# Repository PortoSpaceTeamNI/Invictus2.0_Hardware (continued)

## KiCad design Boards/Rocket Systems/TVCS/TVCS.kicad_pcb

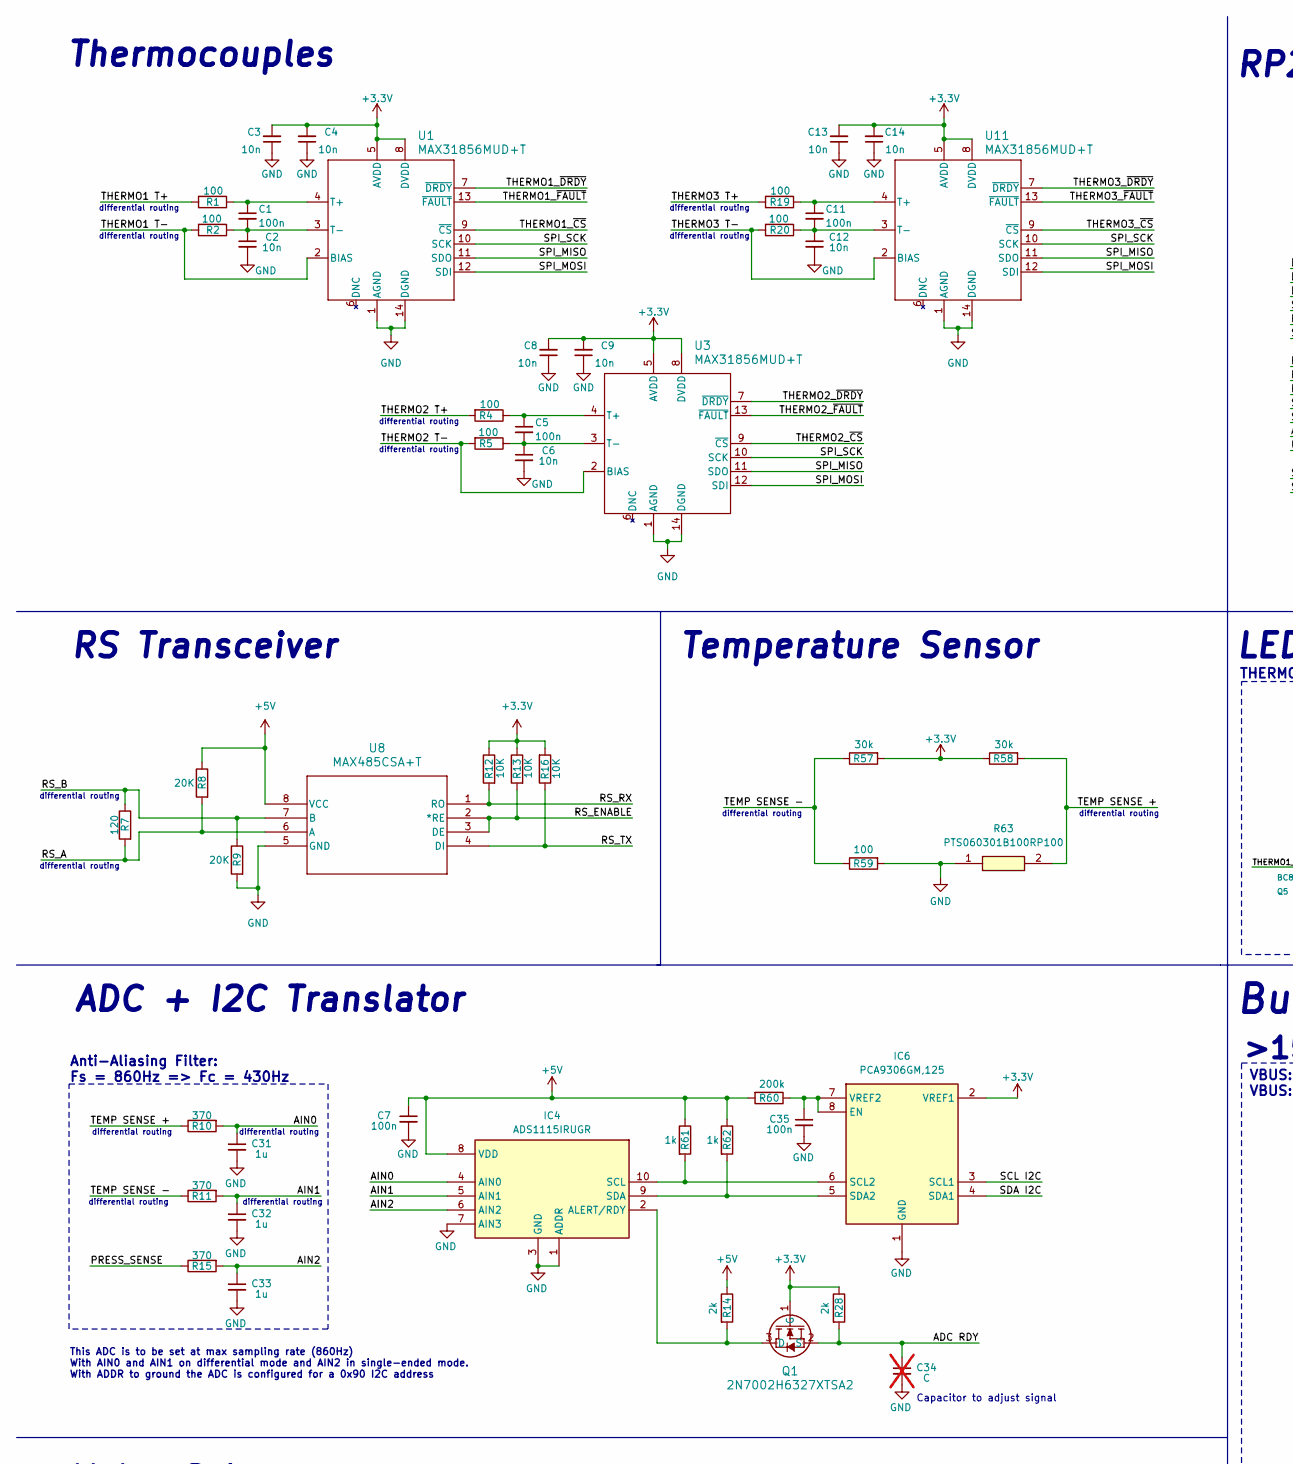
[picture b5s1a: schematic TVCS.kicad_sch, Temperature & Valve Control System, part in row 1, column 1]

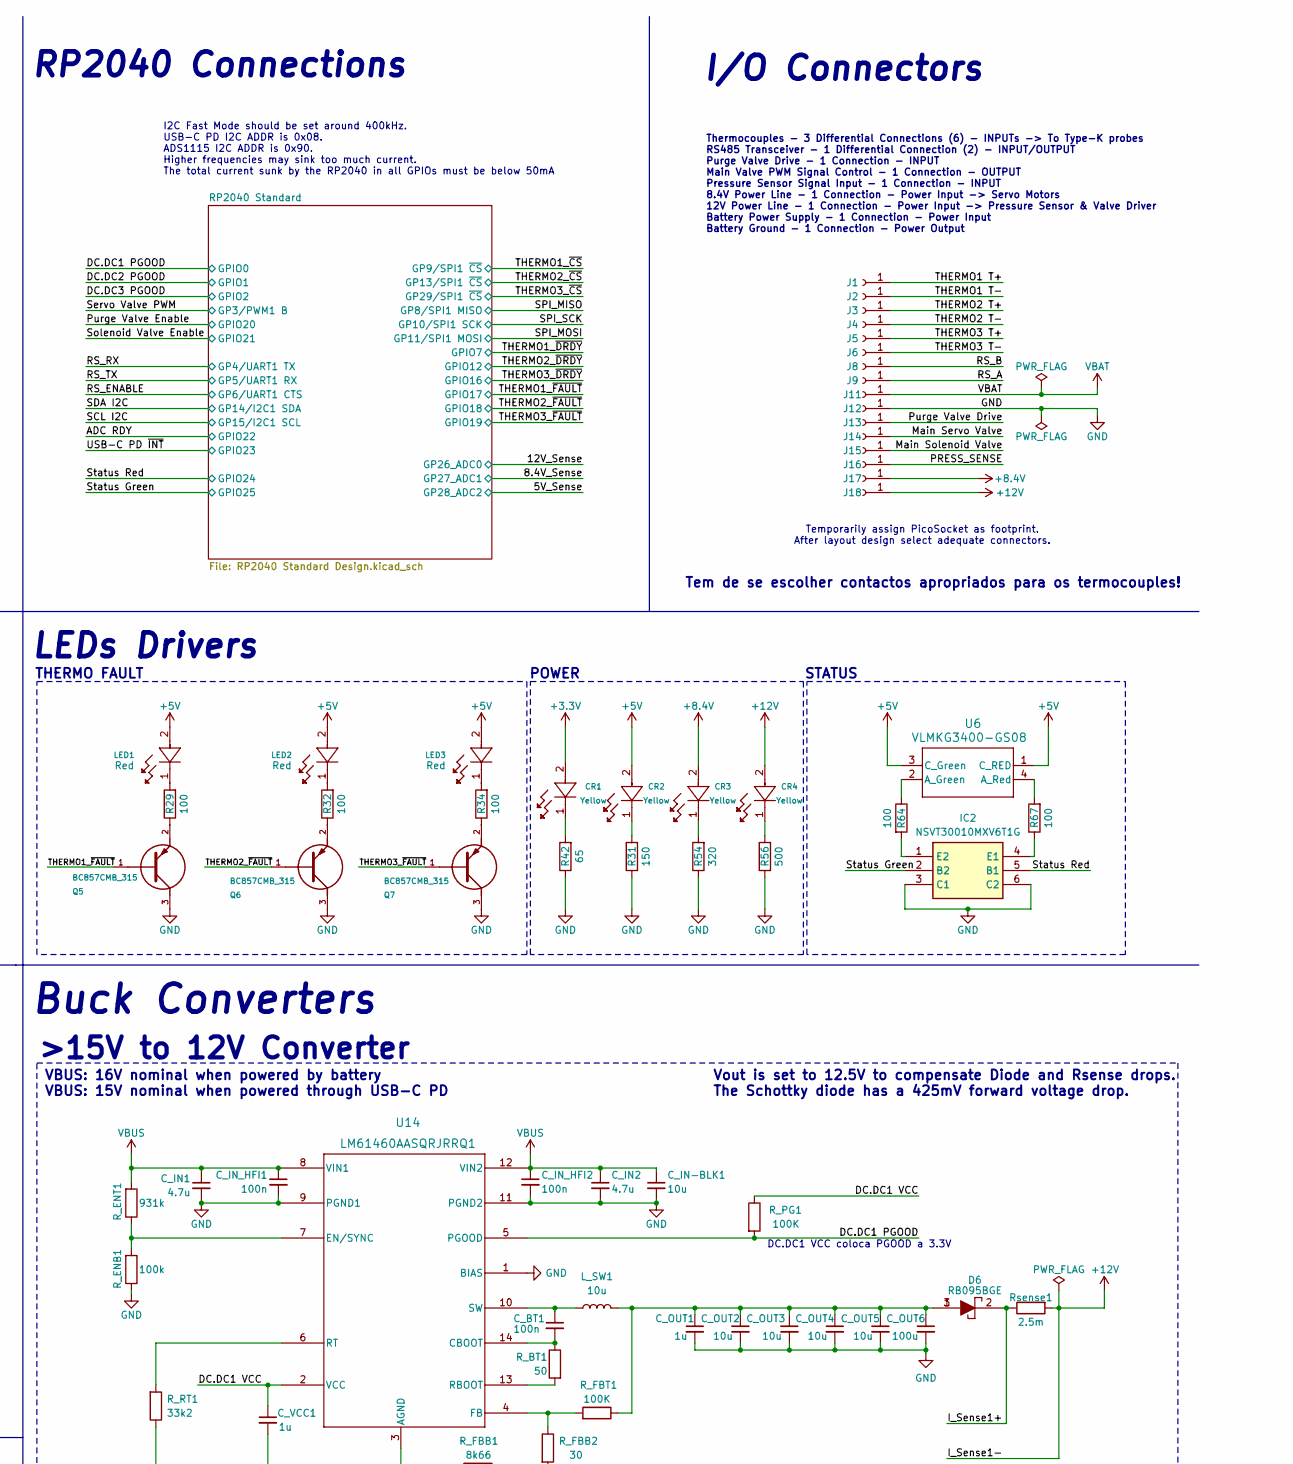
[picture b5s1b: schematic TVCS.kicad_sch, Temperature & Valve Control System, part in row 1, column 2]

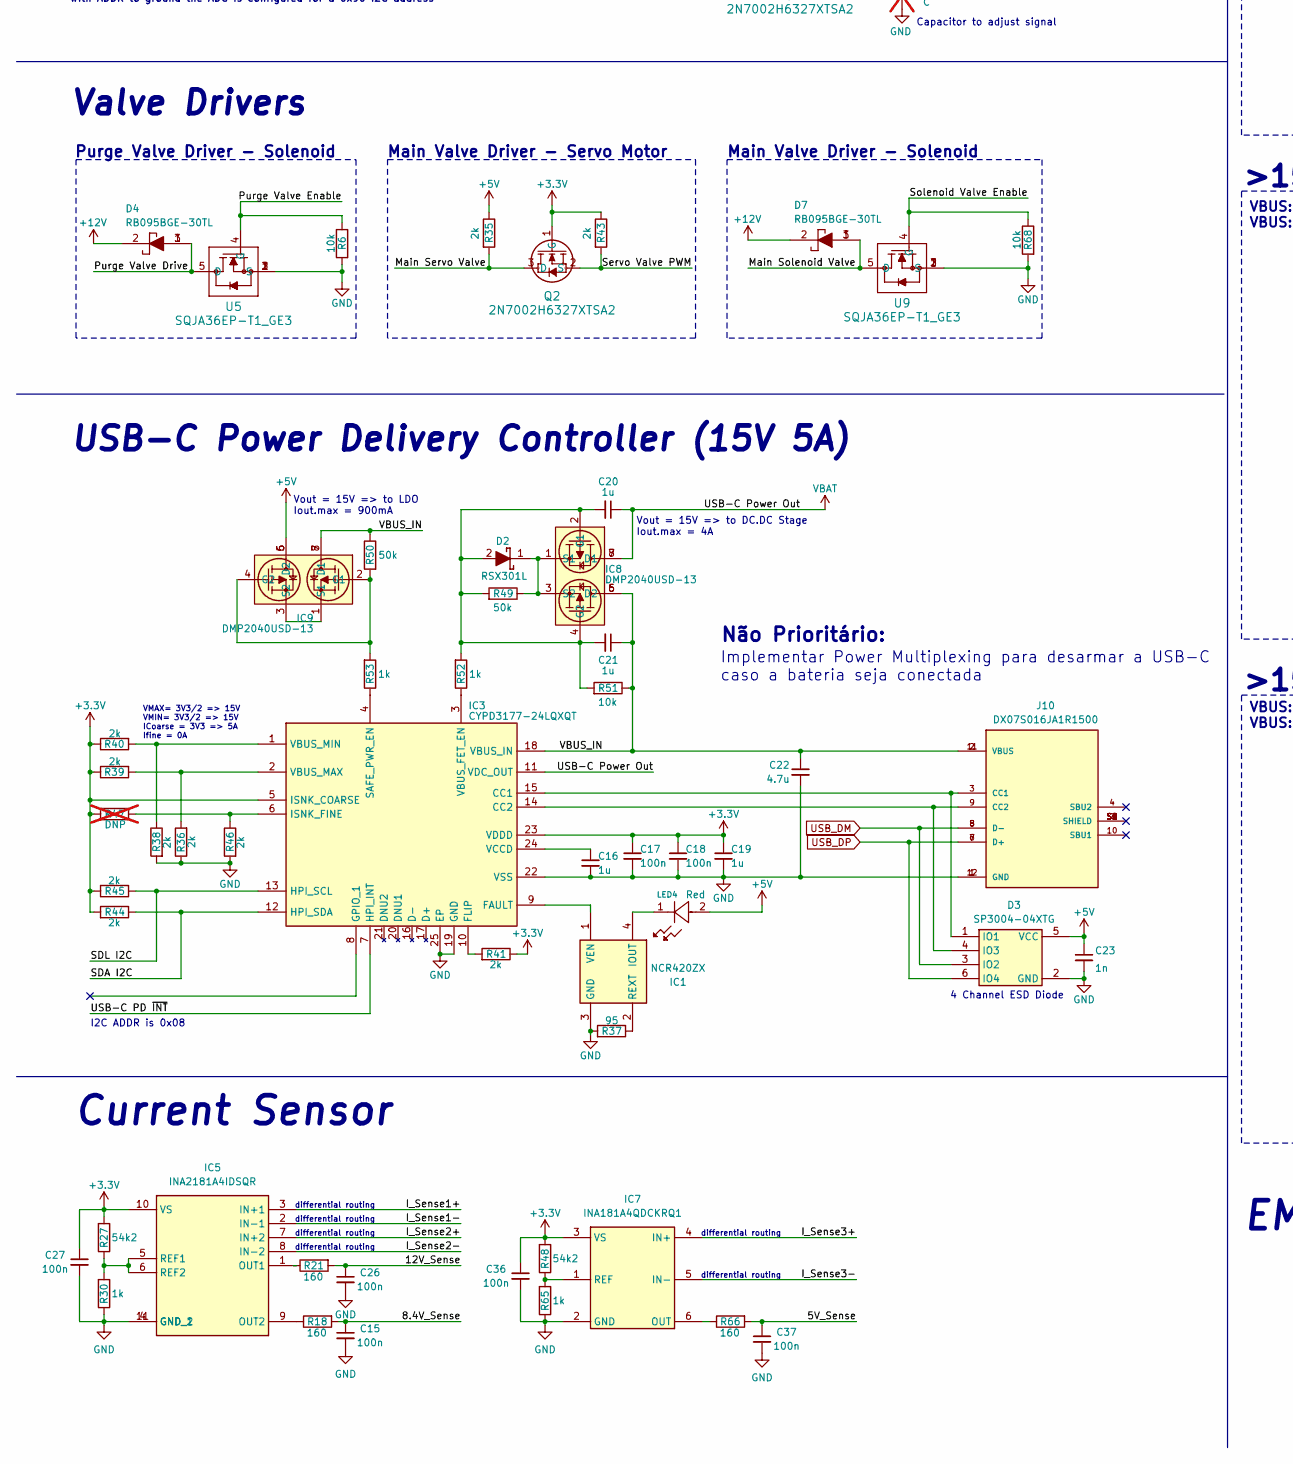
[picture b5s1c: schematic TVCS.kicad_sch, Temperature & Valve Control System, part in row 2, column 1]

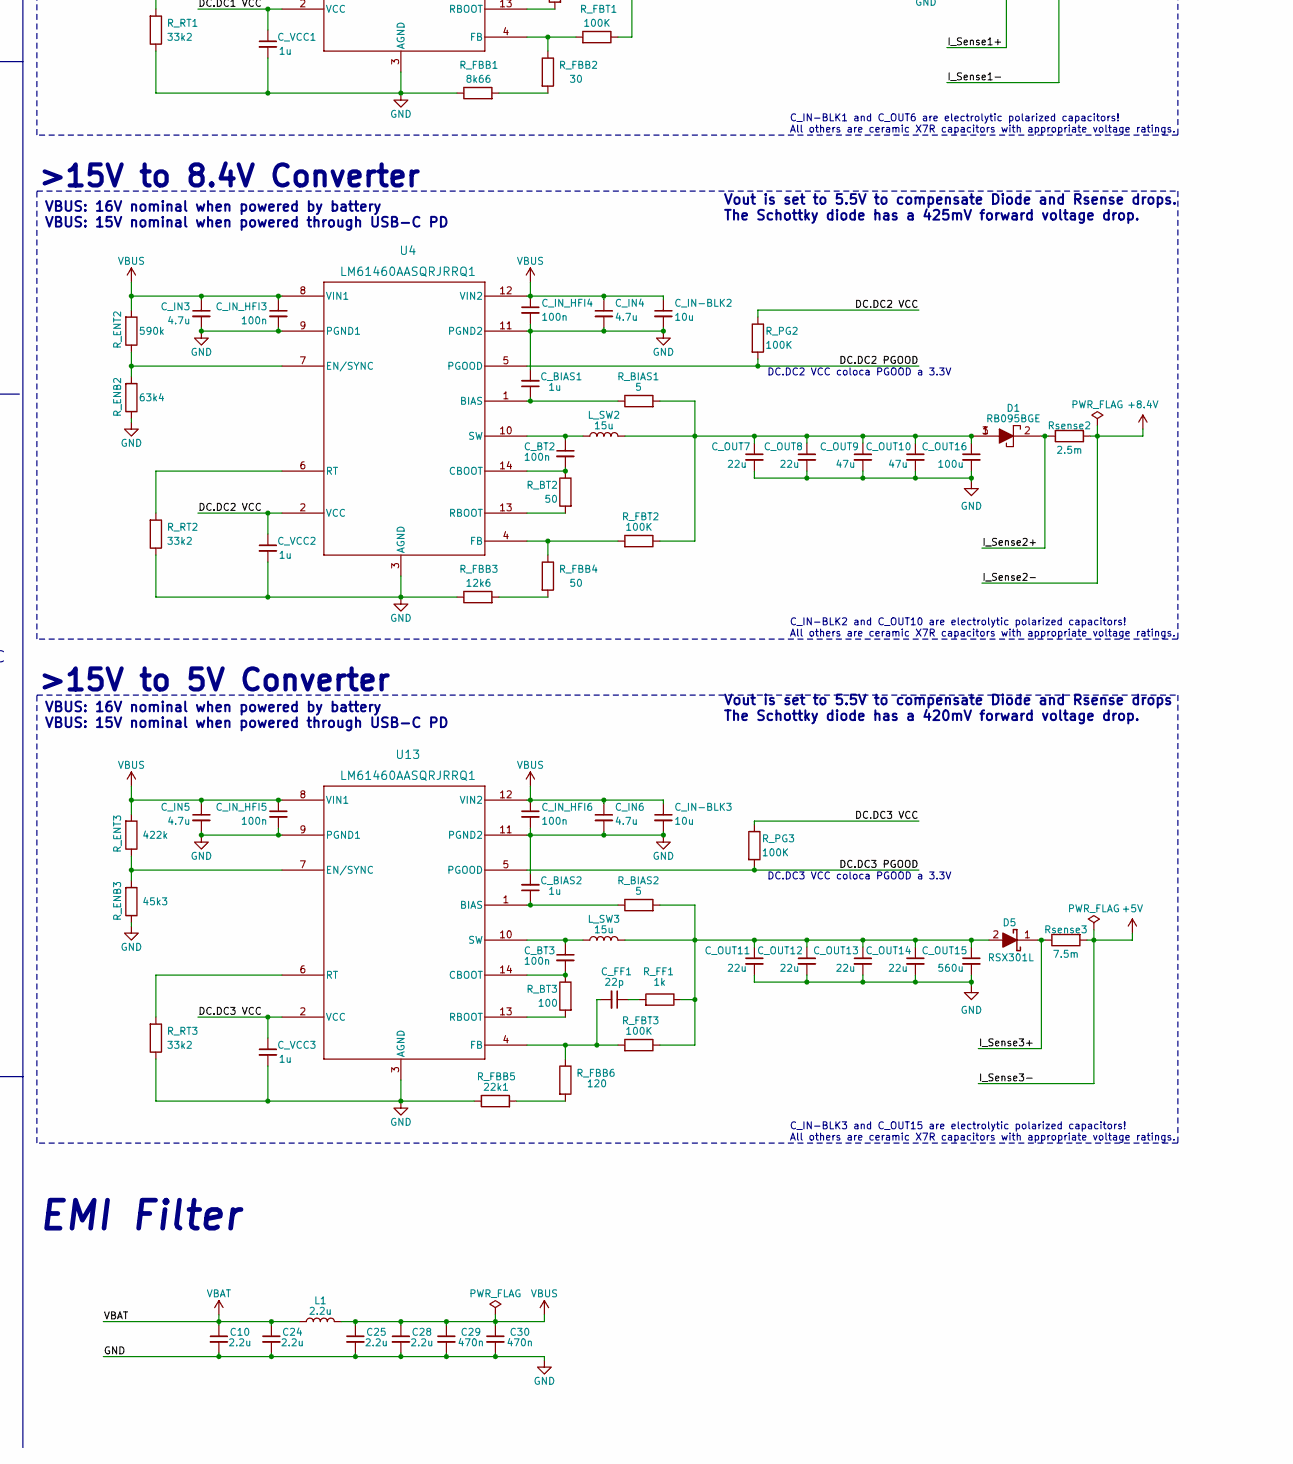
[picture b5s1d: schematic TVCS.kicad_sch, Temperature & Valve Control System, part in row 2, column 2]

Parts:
C1, C5, C7, C11, C15, C17, C18, C26, C27, C35, C36, C37: 100n; Capacitor_0402
C2, C3, C4, C6, C8, C9, C12, C13, C14: 10n; Capacitor_0402
C10, C24, C25, C28: 2.2u; Capacitor_0402
C16, C19, C20, C21: 1u; Capacitor_0603
C22: 4.7u; Capacitor_1206
C23: 1n; Capacitor_0402
C29, C30: 470n; Capacitor_0402
C31, C32, C33: 1u; Capacitor_0402
C34: C; Capacitor_0402; not fitted
CR1, CR2, CR3, CR4: VLMY1300-GS08; LED_VISHAY_VLMX1300_VIS
C_BIAS1, C_BIAS2: 1u; Capacitor_0603
C_BT1, C_BT2, C_BT3: 100n; Capacitor_0402
C_FF1: 22p; Capacitor_0402
C_IN1, C_IN2, C_IN3, C_IN4, C_IN5, C_IN6: 4.7u; Capacitor_1206
C_IN-BLK1, C_IN-BLK2, C_IN-BLK3: 10u; Capacitor_4mm
C_IN_HFI1, C_IN_HFI2, C_IN_HFI3, C_IN_HFI4, C_IN_HFI5, C_IN_HFI6: 100n; Capacitor_0402
C_OUT1: 1u; Capacitor_0603
C_OUT2, C_OUT3, C_OUT4, C_OUT5: 10u; Capacitor_0805
C_OUT6: 100u; Capacitor_6mm
C_OUT7, C_OUT8, C_OUT11, C_OUT12, C_OUT13, C_OUT14: 22u; Capacitor_0805
C_OUT9, C_OUT10: 47u; Capacitor_0805
C_OUT15: 560u; Capacitor_8mm
C_OUT16: 100u; Capacitor_8mm
C_VCC1, C_VCC2, C_VCC3: 1u; Capacitor_0603
D1, D6: RB095BGE; RD3P175SNFRATL; Mouser Part Number 755-RB095BGE-30TL
D2, D5: RSX301L; DIOM5026X220N; Mouser Part Number 755-RSX301L-30DDTE25
D3: SP3004-04XTG; SOT563_LTF; Mouser Part Number 576-SP3004-04XTG
D4, D7: RB095BGE-30TL; RD3P175SNFRATL; Mouser Part Number 755-RB095BGE-30TL
IC1: NCR420ZX; SOT230P700X180-4N; Mouser Part Number 771-NCR420ZX
IC2: NSVT30010MXV6T1G; SOT-563_1P3X1P7_ONS; Mouser Part Number 863-NSVT30010MXV6T1G
IC3: CYPD3177-24LQXQT; QFN50P400X400X60-25N-D; Mouser Part Number 727-CYPD3177-24LQXQT
IC4: ADS1115IRUGR; Mouser Part Number 595-ADS1115IRUGR
IC5: INA2181A4IDSQR; SON40P200X200X80-11N; Mouser Part Number 595-INA2181A4IDSQR
IC6: PCA9306GM,125; PCA9570GMH; Mouser Part Number 771-PCA9306GM125
IC7: INA181A4QDCKRQ1; SOT65P210X110-6N; Mouser Part Number 595-INA181A4QDCKRQ1
IC8, IC9: DMP2040USD-13; SOIC127P600X175-8N; Mouser Part Number 621-DMP2040USD-13
J1, J2, J3, J4, J5, J6, J8, J9, J11, J12, J13, J14, J15, J16, J17, J18: Conn_01x01_Socket; Pico_01pin
J10: DX07S016JA1R1500; JAE_DX07S016JA1R1500; PARTREV 1
L1: 2.2u; Inductor_10.1x10
LED1, LED2, LED3, LED4: VLMS1500-GS08; LED_00-GS08_VIS_RED
L_SW1: 10u; Inductor_11.5x10
L_SW2, L_SW3: 15u; Inductor_10.1x10
Q1, Q2: 2N7002H6327XTSA2; PG-SOT23-3-5_INF_MIN
Q5, Q6, Q7: BC857CMB_315; TRANS_PMZB550UNEYL
R1, R2, R4, R5, R19, R20, R29, R32, R34, R59, R64, R67: 100; RES_0402
R6, R51, R68: 10k; RES_0402
R7: 120; RES_0402
R8, R9: 20K; RES_0402
R10, R11, R15: 370; RES_0402
R12, R13, R16: 10K; RES_0402
R14, R28, R35, R36, R38, R39, R40, R41, R43, R44, R45, R46: 2k; RES_0402
R18, R21, R66: 160; RES_0402
R27, R48: 54k2; RES_0402
R30, R52, R53, R61, R62, R65: 1k; RES_0402
R31: 150; RES_0402
R37: 95; RES_0402
R42: 65; RES_0402
R47: DNP; RES_0402; not fitted
R49, R50: 50k; RES_0402
R54: 320; RES_0402
R56: 500; RES_0402
R57, R58: 30k; RES_0402
R60: 200k; RES_0402
R63: PTS060301B100RP100; RESC1508X55N; Mouser Part Number 594-PTS060301B100RP
R_BIAS1, R_BIAS2: 5; RES_0402
R_BT1, R_BT2: 50; RES_0402
R_BT3: 100; RES_0402
R_ENB1: 100k; RES_0603
R_ENB2: 63k4; RES_0402
R_ENB3: 45k3; RES_0402
R_ENT1: 931k; RES_0603
R_ENT2: 590k; RES_0402
R_ENT3: 422k; RES_0402
R_FBB1: 8k66; RES_0603
R_FBB2: 30; RES_0603
R_FBB3: 12k6; RES_0603
R_FBB4: 50; RES_0603
R_FBB5: 22k1; RES_0603
R_FBB6: 120; RES_0603
R_FBT1, R_FBT2, R_FBT3: 100K; RES_0603
R_FF1: 1k; RES_0402
R_PG1, R_PG2, R_PG3: 100K; RES_0603
R_RT1, R_RT2, R_RT3: 33k2; RES_0603
Rsense1, Rsense2: 2.5m; RES_0805
Rsense3: 7.5m; RES_WSLP2512
U1, U3, U11: MAX31856MUD+T; 21-0066J_14_MXM
U4, U13, U14: LM61460AASQRJRRQ1; VQFN-HR14_RJR_TEX
U5, U9: SQJA36EP-T1_GE3; PowerPAK_SO-8L_3_VIS
U6: VLMKG3400-GS08; SMT_00-GS08_VIS
U8: MAX485CSA+T; 21-0041-3-M_90-0096-8L_MXM

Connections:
+3.3V: C3.2, C4.2, C8.2, C9.2, C13.2, C14.2, C17.1, C18.1, C19.1, C27.1, C36.1, CR1.2, IC3.5 (ISNK_COARSE), IC3.23 (VDDD), IC5.10 (VS), IC6.2 (VREF1), IC7.3 (VS), Q1.1 (G), Q2.1 (G), R12.1, R13.1, R16.2, R27.2, R28.1, R39.1, R40.1, R41.1, R43.1, R44.2, R45.2, R47.2, R48.2, R57.2, R58.1, U1.5 (AVDD), U1.8 (DVDD), U3.5 (AVDD), U3.8 (DVDD), U11.5 (AVDD), U11.8 (DVDD); also elsewhere on the board
+5V: C7.1, C23.1, CR2.2, D3.5 (VCC), IC4.8 (VDD), IC7.5 (IN-), IC9.5 (D2), IC9.6 (D2), LED1.2, LED2.2, LED3.2, LED4.2, R8.1, R14.1, R35.1, R60.2, R61.1, R62.1, Rsense3.2, U6.1 (C_RED), U6.3 (C_Green), U8.8 (VCC); also elsewhere on the board
+8.4V: CR3.2, IC5.8 (IN-2), J17.1, Rsense2.2
+12V: CR4.2, D4.2, D7.2, IC5.2 (IN-1), J18.1, Rsense1.2
/5V_Sense: C37.1, R66.2; also elsewhere on the board
/8.4V_Sense: C15.1, R18.2; also elsewhere on the board
/12V_Sense: C26.1, R21.2; also elsewhere on the board
/ADC RDY: C34.1, Q1.2 (S), R28.2; also elsewhere on the board
/AIN0: C31.1, IC4.4 (AIN0), R10.2
/AIN1: C32.1, IC4.5 (AIN1), R11.2
/AIN2: C33.1, IC4.6 (AIN2), R15.2
/DC.DC1 PGOOD: R_PG1.2, U14.5 (PGOOD); also elsewhere on the board
/DC.DC1 VCC: C_VCC1.1, R_PG1.1, U14.2 (VCC)
/DC.DC2 PGOOD: R_PG2.2, U4.5 (PGOOD); also elsewhere on the board
/DC.DC2 VCC: C_VCC2.1, R_PG2.1, U4.2 (VCC)
/DC.DC3 PGOOD: R_PG3.2, U13.5 (PGOOD); also elsewhere on the board
/DC.DC3 VCC: C_VCC3.1, R_PG3.1, U13.2 (VCC)
/I_Sense1+: D6.2, IC5.3 (IN+1), Rsense1.1
/I_Sense2+: D1.2, IC5.7 (IN+2), Rsense2.1
/I_Sense3+: D5.1 (K), IC7.4 (IN+), Rsense3.1
/Main Servo Valve: J14.1, Q2.3 (D), R35.2
/Main Solenoid Valve: D7.1, D7.3, J15.1, U9.5 (D)
/PRESS_SENSE: J16.1, R15.1
/Purge Valve Drive: D4.1, D4.3, J13.1, U5.5 (D)
/Purge Valve Enable: R6.1, U5.4 (G); also elsewhere on the board
/RS_A: J9.1, R7.2, R8.2, U8.6 (A)
/RS_B: J8.1, R7.1, R9.1, U8.7 (B)
/RS_ENABLE: R13.2, U8.2 (*RE), U8.3 (DE); also elsewhere on the board
/RS_RX: R12.2, U8.1 (RO); also elsewhere on the board
/RS_TX: R16.1, U8.4 (DI); also elsewhere on the board
/SCL I2C: IC6.3 (SCL1); also elsewhere on the board
/SDA I2C: IC3.12 (HPI_SDA), IC6.4 (SDA1), R44.1; also elsewhere on the board
/SDL I2C: IC3.13 (HPI_SCL), R45.1
/SPI_MISO: U1.11 (SDO), U3.11 (SDO), U11.11 (SDO); also elsewhere on the board
/SPI_MOSI: U1.12 (SDI), U3.12 (SDI), U11.12 (SDI); also elsewhere on the board
/SPI_SCK: U1.10 (SCK), U3.10 (SCK), U11.10 (SCK); also elsewhere on the board
/Servo Valve PWM: Q2.2 (S), R43.2; also elsewhere on the board
/Solenoid Valve Enable: R68.1, U9.4 (G); also elsewhere on the board
/Status Green: IC2.2 (B2); also elsewhere on the board
/Status Red: IC2.5 (B1); also elsewhere on the board
/TEMP SENSE +: R10.1, R58.2, R63.2
/TEMP SENSE -: R11.1, R57.1, R59.1
/THERMO1 T+: J1.1, R1.2
/THERMO1 T-: J2.1, R2.2, U1.2 (BIAS)
/THERMO1_~CS: U1.9 (~CS); also elsewhere on the board
/THERMO1_~DRDY: U1.7 (~DRDY); also elsewhere on the board
/THERMO1_~FAULT: Q5.1, U1.13 (~FAULT); also elsewhere on the board
/THERMO2 T+: J3.1, R4.2
/THERMO2 T-: J4.1, R5.2, U3.2 (BIAS)
/THERMO2_~CS: U3.9 (~CS); also elsewhere on the board
/THERMO2_~DRDY: U3.7 (~DRDY); also elsewhere on the board
/THERMO2_~FAULT: Q6.1, U3.13 (~FAULT); also elsewhere on the board
/THERMO3 T+: J5.1, R19.2
/THERMO3 T-: J6.1, R20.2, U11.2 (BIAS)
/THERMO3_~CS: U11.9 (~CS); also elsewhere on the board
/THERMO3_~DRDY: U11.7 (~DRDY); also elsewhere on the board
/THERMO3_~FAULT: Q7.1, U11.13 (~FAULT); also elsewhere on the board
/USB-C PD ~INT: IC3.7 (HPI_INT); also elsewhere on the board
/VBUS_IN: C21.1, C22.1, IC3.18 (VBUS_IN), IC8.5 (D2), IC8.6 (D2), IC9.7 (D1), IC9.8 (D1), J10.2 (VBUS), J10.11 (VBUS), R50.1, R51.1
GND: C2.2, C3.1, C4.1, C6.2, C7.2, C8.1, C9.1, C10.2, C12.2, C13.1, C14.1, C15.2, C16.2, C17.2, C18.2, C19.2, C22.2, C23.2, C24.2, C25.2, C26.2, C27.2, C28.2, C29.2, C30.2, C31.2, C32.2, C33.2, C34.2, C35.2, C36.2, C37.2, C_BIAS1.2, C_BIAS2.2, C_IN1.2, C_IN2.2, C_IN3.2, C_IN4.2, C_IN5.2, C_IN6.2, C_IN-BLK1.2, C_IN-BLK2.2, C_IN-BLK3.2, C_IN_HFI1.2, C_IN_HFI2.2, C_IN_HFI3.2, C_IN_HFI4.2, C_IN_HFI5.2, C_IN_HFI6.2, C_OUT1.2, C_OUT2.2, C_OUT3.2, C_OUT4.2, C_OUT5.2, C_OUT6.2, C_OUT7.2, C_OUT8.2, C_OUT9.2, C_OUT10.2, C_OUT11.2, C_OUT12.2, C_OUT13.2, C_OUT14.2, C_OUT15.2, C_OUT16.2, C_VCC1.2, C_VCC2.2, C_VCC3.2, D3.2 (GND), IC1.3 (GND), IC2.3 (C1), IC2.6 (C2), IC3.19 (GND), IC3.22 (VSS), IC3.25 (EP), IC4.1 (ADDR), IC4.3 (GND), IC4.7 (AIN3), IC5.4 (GND_1), IC5.11 (GND_2), IC6.1 (GND), IC7.2 (GND), J10.1 (GND), J10.12 (GND), J12.1, Q5.3, Q6.3, Q7.3, R6.2, R9.2, R30.1, R31.1, R36.1, R37.2, R38.2, R42.1, R46.2, R54.1, R56.1, R59.2, R63.1, R65.1, R68.2, R_ENB1.1, R_ENB2.1, R_ENB3.1, R_FBB1.1, R_FBB3.1, R_FBB5.1, R_RT1.1, R_RT2.1, R_RT3.1, U1.1 (AGND), U1.14 (DGND), U3.1 (AGND), U3.14 (DGND), U4.3 (AGND), U4.9 (PGND1), U4.11 (PGND2), U5.1 (S), U5.2 (S), U5.3 (S), U8.5 (GND), U9.1 (S), U9.2 (S), U9.3 (S), U11.1 (AGND), U11.14 (DGND), U13.3 (AGND), U13.9 (PGND1), U13.11 (PGND2), U14.1 (BIAS), U14.3 (AGND), U14.9 (PGND1), U14.11 (PGND2); also elsewhere on the board
unnamed: CR1.1, R42.2
unnamed: CR2.1, R31.2
unnamed: CR3.1, R54.2
unnamed: CR4.1, R56.2
unnamed: C_FF1.1, R_FF1.2
unnamed: C_OUT1.1, C_OUT2.1, C_OUT3.1, C_OUT4.1, C_OUT5.1, C_OUT6.1, D6.1, D6.3, L_SW1.2, R_FBT1.1
unnamed: C_OUT7.1, C_OUT8.1, C_OUT9.1, C_OUT10.1, C_OUT16.1, D1.1, D1.3, L_SW2.2, R_BIAS1.2, R_FBT2.1
unnamed: C20.2, C21.2, D2.2 (A), IC8.2 (G1), IC8.4 (G2), R49.2, R51.2, R52.2
unnamed: D2.1 (K), IC8.1 (S1), IC8.3 (S2), R49.1
unnamed: D3.1 (IO1), IC3.15 (CC1), J10.3 (CC1)
unnamed: D3.4 (IO3), IC3.14 (CC2), J10.9 (CC2)
unnamed: C_OUT11.1, C_OUT12.1, C_OUT13.1, C_OUT14.1, C_OUT15.1, D5.2 (A), L_SW3.2, R_BIAS2.2, R_FBT3.1, R_FF1.1
unnamed: IC1.4 (IOUT), LED4.1
unnamed: IC1.2 (REXT), R37.1
unnamed: IC1.1 (VEN), IC3.9 (FAULT)
unnamed: IC2.4 (E1), R67.1
unnamed: IC2.1 (E2), R64.2
unnamed: IC3.10 (FLIP), R41.2
unnamed: IC3.6 (ISNK_FINE), R46.1, R47.1
unnamed: IC3.4 (SAFE_PWR_EN), R53.1
unnamed: IC3.3 (VBUS_FET_EN), R52.1
unnamed: IC3.2 (VBUS_MAX), R36.2, R39.2
unnamed: IC3.1 (VBUS_MIN), R38.1, R40.2
unnamed: C16.1, IC3.24 (VCCD)
unnamed: IC4.2 (ALERT/RDY), Q1.3 (D), R14.2
unnamed: IC4.10 (SCL), IC6.6 (SCL2), R61.2
unnamed: IC4.9 (SDA), IC6.5 (SDA2), R62.2
unnamed: IC5.1 (OUT1), R21.1
unnamed: IC5.9 (OUT2), R18.1
unnamed: IC5.5 (REF1), IC5.6 (REF2), R27.1, R30.2
unnamed: C35.1, IC6.7 (VREF2), IC6.8 (EN), R60.1
unnamed: IC7.6 (OUT), R66.1
unnamed: IC7.1 (REF), R48.1, R65.2
unnamed: IC9.2 (G1), IC9.4 (G2), R50.2, R53.2
unnamed: IC9.1 (S1), IC9.3 (S2)
unnamed: LED1.1, R29.2
unnamed: LED2.1, R32.2
unnamed: LED3.1, R34.2
unnamed: Q5.2, R29.1
unnamed: Q6.2, R32.1
unnamed: Q7.2, R34.1
unnamed: R_FBB1.2, R_FBB2.2
unnamed: R_FBB3.2, R_FBB4.2
unnamed: R_FBB5.2, R_FBB6.2
unnamed: C1.1, R1.1, U1.4 (T+)
unnamed: C1.2, C2.1, R2.1, U1.3 (T-)
unnamed: C5.1, R4.1, U3.4 (T+)
unnamed: C5.2, C6.1, R5.1, U3.3 (T-)
unnamed: C_BIAS1.1, R_BIAS1.1, U4.1 (BIAS)
unnamed: C_BT2.2, R_BT2.1, U4.14 (CBOOT)
unnamed: R_ENB2.2, R_ENT2.1, U4.7 (EN/SYNC)
unnamed: R_FBB4.1, R_FBT2.2, U4.4 (FB)
unnamed: R_BT2.2, U4.13 (RBOOT)
unnamed: R_RT2.2, U4.6 (RT)
unnamed: C_BT2.1, L_SW2.1, U4.10 (SW)
unnamed: R64.1, U6.2 (A_Green)
unnamed: R67.2, U6.4 (A_Red)
unnamed: C11.1, R19.1, U11.4 (T+)
unnamed: C11.2, C12.1, R20.1, U11.3 (T-)
unnamed: C_BIAS2.1, R_BIAS2.1, U13.1 (BIAS)
unnamed: C_BT3.2, R_BT3.1, U13.14 (CBOOT)
unnamed: R_ENB3.2, R_ENT3.1, U13.7 (EN/SYNC)
unnamed: C_FF1.2, R_FBB6.1, R_FBT3.2, U13.4 (FB)
unnamed: R_BT3.2, U13.13 (RBOOT)
unnamed: R_RT3.2, U13.6 (RT)
unnamed: C_BT3.1, L_SW3.1, U13.10 (SW)
unnamed: C_BT1.2, R_BT1.1, U14.14 (CBOOT)
unnamed: R_ENB1.2, R_ENT1.1, U14.7 (EN/SYNC)
unnamed: R_FBB2.1, R_FBT1.2, U14.4 (FB)
unnamed: R_BT1.2, U14.13 (RBOOT)
unnamed: R_RT1.2, U14.6 (RT)
unnamed: C_BT1.1, L_SW1.1, U14.10 (SW)
USB_DM: D3.3 (IO2), J10.5 (D-), J10.8 (D-); also elsewhere on the board
USB_DP: D3.6 (IO4), J10.6 (D+), J10.7 (D+); also elsewhere on the board
VBAT: C10.1, C20.1, C24.1, IC3.11 (VDC_OUT), IC8.7 (D1), IC8.8 (D1), J11.1, L1.1
VBUS: C25.1, C28.1, C29.1, C30.1, C_IN1.1, C_IN2.1, C_IN3.1, C_IN4.1, C_IN5.1, C_IN6.1, C_IN-BLK1.1, C_IN-BLK2.1, C_IN-BLK3.1, C_IN_HFI1.1, C_IN_HFI2.1, C_IN_HFI3.1, C_IN_HFI4.1, C_IN_HFI5.1, C_IN_HFI6.1, L1.2, R_ENT1.2, R_ENT2.2, R_ENT3.2, U4.8 (VIN1), U4.12 (VIN2), U13.8 (VIN1), U13.12 (VIN2), U14.8 (VIN1), U14.12 (VIN2)

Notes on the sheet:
C_IN-BLK2 and C_OUT10 are electrolytic polarized capacitors! All others are ceramic X7R capacitors with appropriate voltage ratings.
VBUS: 16V nominal when powered by battery VBUS: 15V nominal when powered through USB-C PD
differential routing
DC.DC3 VCC coloca PGOOD a 3.3V
RS Transceiver
Main Valve Driver - Servo Motor
RP2040 Connections
Não Prioritário:
Vout is set to 5.5V to compensate Diode and Rsense drops. The Schottky diode has a 425mV forward voltage drop.
Thermocouples
C_IN-BLK3 and C_OUT15 are electrolytic polarized capacitors! All others are ceramic X7R capacitors with appropriate voltage ratings.
POWER
I2C Fast Mode should be set around 400kHz. USB-C PD I2C ADDR is 0x08. ADS1115 I2C ADDR is 0x90. Higher frequencies may sink too much current. The total current sunk by the RP2040 in all GPIOs must be below 50mA
DC.DC2 VCC coloca PGOOD a 3.3V
Tem de se escolher contactos apropriados para os termocouples!
Valve Drivers
>15V to 12V Converter
C_IN-BLK1 and C_OUT6 are electrolytic polarized capacitors! All others are ceramic X7R capacitors with appropriate voltage ratings.
Temporarily assign PicoSocket as footprint. After layout design select adequate connectors.
LEDs Drivers
ADC + I2C Translator
Implementar Power Multiplexing para desarmar a USB-C caso a bateria seja conectada
4 Channel ESD Diode
Capacitor to adjust signal
THERMO FAULT
Vout = 15V => to DC.DC Stage Iout.max = 4A
>15V to 8.4V Converter
Buck Converters
EMI Filter
Purge Valve Driver - Solenoid
Vout is set to 5.5V to compensate Diode and Rsense drops The Schottky diode has a 420mV forward voltage drop.
Temperature Sensor
STATUS
Main Valve Driver - Solenoid
This ADC is to be set at max sampling rate (860Hz) With AIN0 and AIN1 on differential mode and AIN2 in single-ended mode. With ADDR to ground the ADC is configured for a 0x90 I2C address
Vout = 15V => to LDO Iout.max = 900mA
VMAX= 3V3/2 => 15V VMIN= 3V3/2 => 15V ICoarse = 3V3 => 5A Ifine = 0A
Thermocouples - 3 Differential Connections (6) - INPUTs -> To Type-K probes RS485 Transceiver - 1 Differential Connection (2) - INPUT/OUTPUT Purge Valve Drive - 1 Connection - INPUT Main Valve PWM Signal Control - 1 Connection - OUTPUT Pressure Sensor Signal Input - 1 Connection - INPUT 8.4V Power 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
Anti-Aliasing Filter: Fs = 860Hz => Fc = 430Hz
DC.DC1 VCC coloca PGOOD a 3.3V

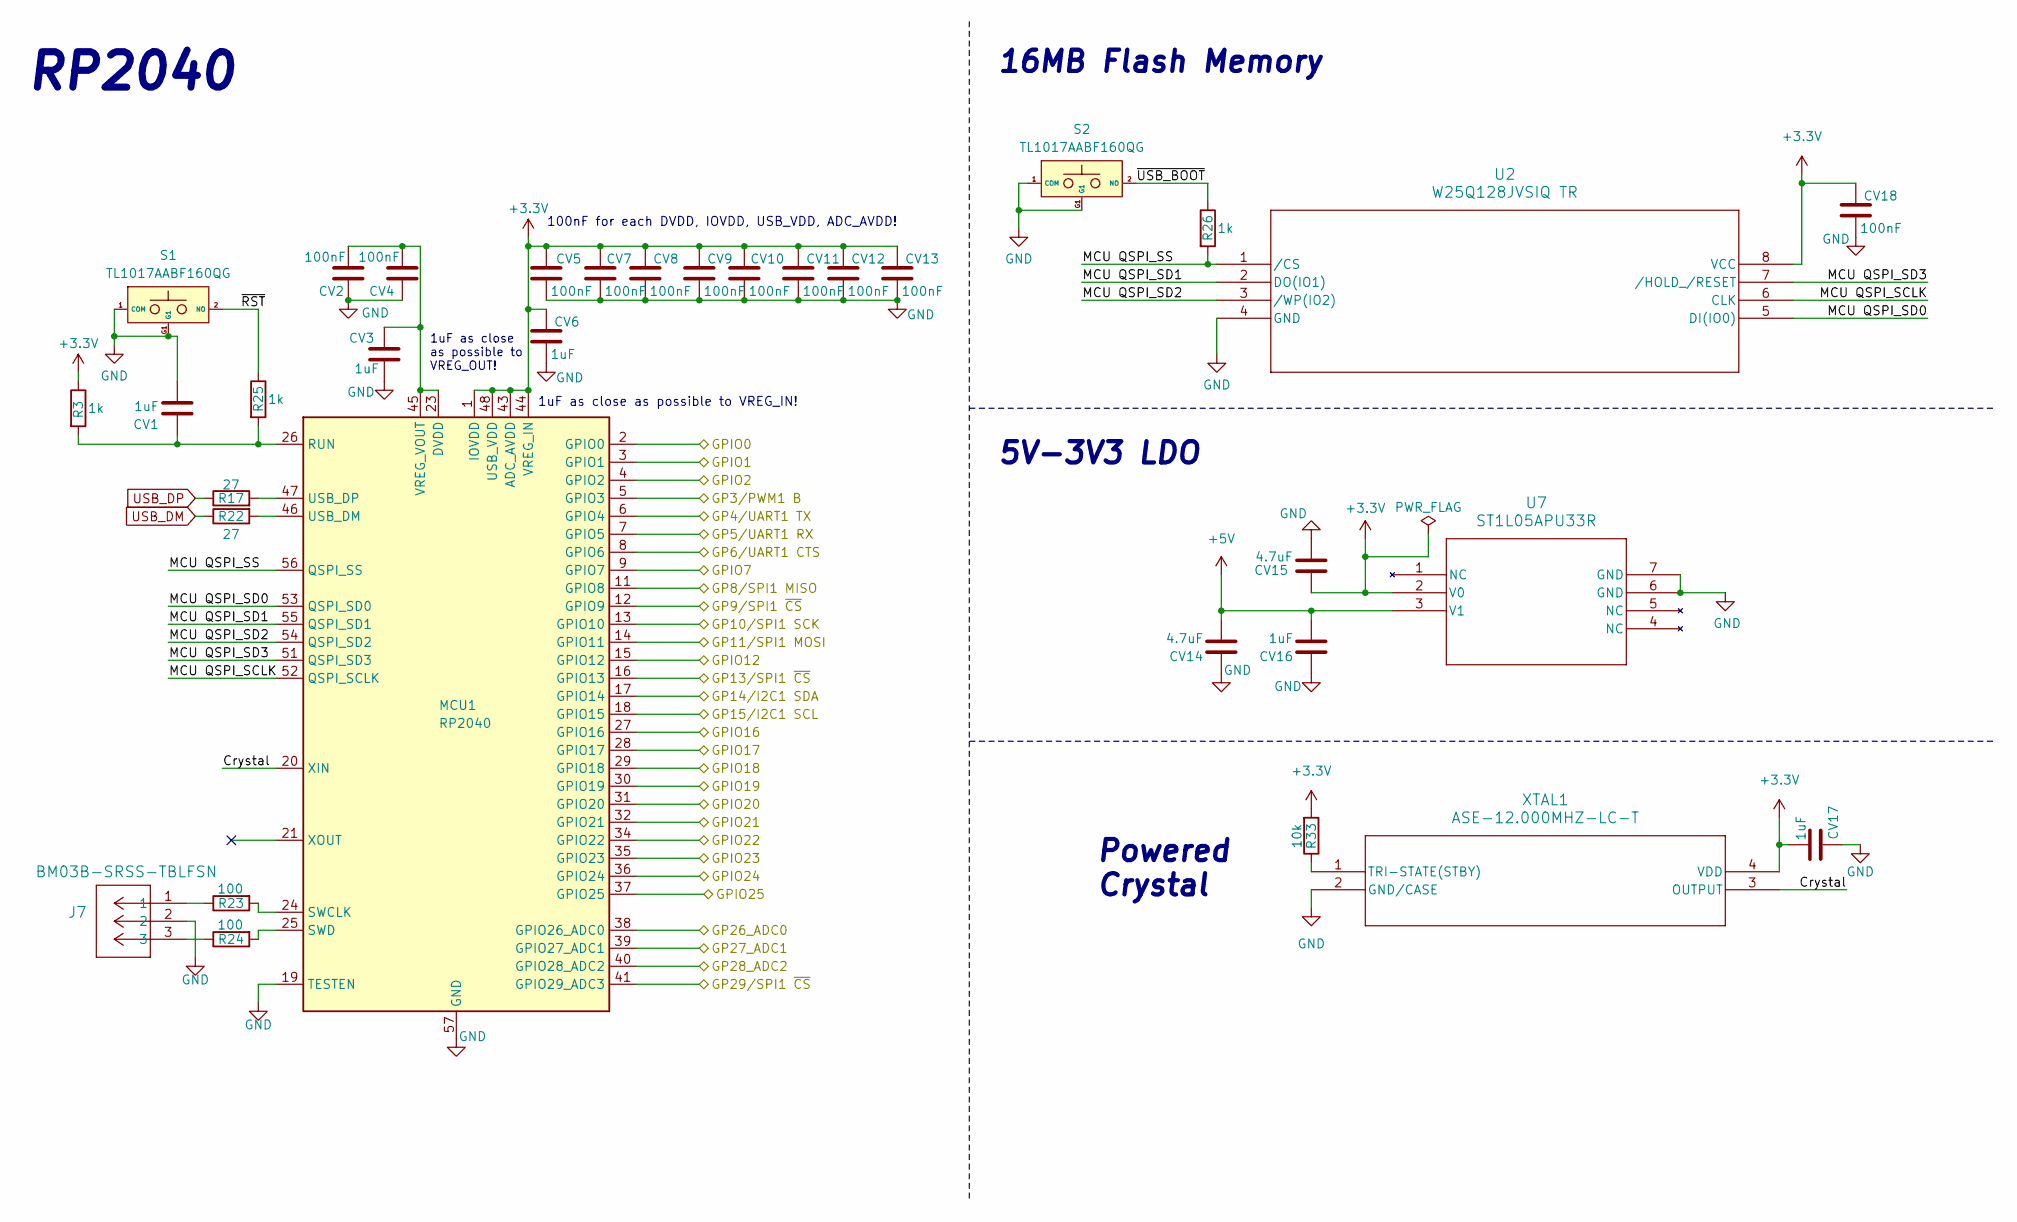
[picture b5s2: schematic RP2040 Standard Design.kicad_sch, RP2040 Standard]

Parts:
CV1, CV3, CV6, CV16, CV17: 1uF; Capacitor_0402
CV2, CV4, CV5, CV7, CV8, CV9, CV10, CV11, CV12, CV13, CV18: 100nF; Capacitor_0402
CV14, CV15: 4.7uF; Capacitor_0402
J7: BM03B-SRSS-TBLFSN; CONN_BM03B-SRSS-TBLFSN_JST
MCU1: RP2040; QFN-56-1EP_7x7mm_P0.4mm_EP3.2x3.2mm
R3, R25, R26: 1k; RES_0402
R17, R22: 27; RES_0603
R23, R24: 100; RES_0402
R33: 10k; RES_0402
S1, S2: TL1017AABF160QG; Mouser Part Number 612-TL1017AABF160QG
U2: W25Q128JVSIQ TR; SOIC_208MIL_WIN
U7: ST1L05APU33R; DFN_5APU33R_STM
XTAL1: ASE-12.000MHZ-LC-T; ASE-3.2X2.5_ABR

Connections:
+3.3V: CV5.1, CV6.1, CV7.1, CV8.1, CV9.1, CV10.1, CV11.1, CV12.1, CV13.1, CV15.2, CV17.1, CV18.1, MCU1.1 (IOVDD), MCU1.10 (IOVDD), MCU1.22 (IOVDD), MCU1.33 (IOVDD), MCU1.42 (IOVDD), MCU1.43 (ADC_AVDD), MCU1.44 (VREG_IN), MCU1.48 (USB_VDD), MCU1.49 (IOVDD), R3.1, R33.2, U2.8 (VCC), U7.2 (V0), XTAL1.4 (VDD); also elsewhere on the board
+5V: CV14.2, CV16.2, U7.3 (V1); also elsewhere on the board
/5V_Sense: MCU1.40 (GPIO28_ADC2); also elsewhere on the board
/8.4V_Sense: MCU1.39 (GPIO27_ADC1); also elsewhere on the board
/12V_Sense: MCU1.38 (GPIO26_ADC0); also elsewhere on the board
/ADC RDY: MCU1.34 (GPIO22); also elsewhere on the board
/DC.DC1 PGOOD: MCU1.2 (GPIO0); also elsewhere on the board
/DC.DC2 PGOOD: MCU1.3 (GPIO1); also elsewhere on the board
/DC.DC3 PGOOD: MCU1.4 (GPIO2); also elsewhere on the board
/Purge Valve Enable: MCU1.31 (GPIO20); also elsewhere on the board
/RP2040 Standard/Crystal: MCU1.20 (XIN), XTAL1.3 (OUTPUT)
/RP2040 Standard/MCU QSPI_SCLK: MCU1.52 (QSPI_SCLK), U2.6 (CLK)
/RP2040 Standard/MCU QSPI_SD0: MCU1.53 (QSPI_SD0), U2.5 (DI(IO0))
/RP2040 Standard/MCU QSPI_SD1: MCU1.55 (QSPI_SD1), U2.2 (DO(IO1))
/RP2040 Standard/MCU QSPI_SD2: MCU1.54 (QSPI_SD2), U2.3 (/WP(IO2))
/RP2040 Standard/MCU QSPI_SD3: MCU1.51 (QSPI_SD3), U2.7 (/HOLD_/RESET)
/RP2040 Standard/MCU QSPI_SS: MCU1.56 (QSPI_SS), R26.2, U2.1 (/CS)
/RP2040 Standard/~RST: R25.1, S1.2 (NO)
/RP2040 Standard/~USB_BOOT: R26.1, S2.2 (NO)
/RS_ENABLE: MCU1.8 (GPIO6); also elsewhere on the board
/RS_RX: MCU1.6 (GPIO4); also elsewhere on the board
/RS_TX: MCU1.7 (GPIO5); also elsewhere on the board
/SCL I2C: MCU1.18 (GPIO15); also elsewhere on the board
/SDA I2C: MCU1.17 (GPIO14); also elsewhere on the board
/SPI_MISO: MCU1.11 (GPIO8); also elsewhere on the board
/SPI_MOSI: MCU1.14 (GPIO11); also elsewhere on the board
/SPI_SCK: MCU1.13 (GPIO10); also elsewhere on the board
/Servo Valve PWM: MCU1.5 (GPIO3); also elsewhere on the board
/Solenoid Valve Enable: MCU1.32 (GPIO21); also elsewhere on the board
/Status Green: MCU1.37 (GPIO25); also elsewhere on the board
/Status Red: MCU1.36 (GPIO24); also elsewhere on the board
/THERMO1_~CS: MCU1.12 (GPIO9); also elsewhere on the board
/THERMO1_~DRDY: MCU1.9 (GPIO7); also elsewhere on the board
/THERMO1_~FAULT: MCU1.28 (GPIO17); also elsewhere on the board
/THERMO2_~CS: MCU1.16 (GPIO13); also elsewhere on the board
/THERMO2_~DRDY: MCU1.15 (GPIO12); also elsewhere on the board
/THERMO2_~FAULT: MCU1.29 (GPIO18); also elsewhere on the board
/THERMO3_~CS: MCU1.41 (GPIO29_ADC3); also elsewhere on the board
/THERMO3_~DRDY: MCU1.27 (GPIO16); also elsewhere on the board
/THERMO3_~FAULT: MCU1.30 (GPIO19); also elsewhere on the board
/USB-C PD ~INT: MCU1.35 (GPIO23); also elsewhere on the board
GND: CV1.2, CV2.1, CV3.2, CV4.1, CV5.2, CV6.2, CV7.2, CV8.2, CV9.2, CV10.2, CV11.2, CV12.2, CV13.2, CV14.1, CV15.1, CV16.1, CV17.2, CV18.2, J7.2, MCU1.19 (TESTEN), MCU1.57 (GND), S1.1 (COM), S1.G1, S2.1 (COM), S2.G1, U2.4 (GND), U7.6 (GND), U7.7 (GND), XTAL1.2 (GND/CASE); also elsewhere on the board
unnamed: J7.1, R23.1
unnamed: J7.3, R24.1
unnamed: CV1.1, MCU1.26 (RUN), R3.2, R25.2
unnamed: MCU1.24 (SWCLK), R23.2
unnamed: MCU1.25 (SWD), R24.2
unnamed: MCU1.46 (USB_DM), R22.2
unnamed: MCU1.47 (USB_DP), R17.2
unnamed: CV2.2, CV3.1, CV4.2, MCU1.23 (DVDD), MCU1.45 (VREG_VOUT), MCU1.50 (DVDD)
unnamed: R33.1, XTAL1.1 (TRI-STATE(STBY))
USB_DM: R22.1; also elsewhere on the board
USB_DP: R17.1; also elsewhere on the board

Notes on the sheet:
Powered Crystal
1uF as close as possible to VREG_IN!
1uF as close as possible to VREG_OUT!
RP2040
100nF for each DVDD, IOVDD, USB_VDD, ADC_AVDD!
5V-3V3 LDO
16MB Flash Memory

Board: 4 copper layers, 259 parts (0 on the bottom side), 154 nets, no tracks yet.
